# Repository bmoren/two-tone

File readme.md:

# two tone

I wanted to work on building a simple module from start to finish to test out some panel fab ideas and I thought a LPG/LPF would be a good candidate. After listening to Why We Bleep Ep.2 with Abstract Data and talking about the character of imperfection in analog circuits, I thought making a DIY vactrol based board would be interesting! I also thought if there were 2 halves, you could use slightly different components and vary each to make them truly distinct from one another. You can get different characteristics in the filter depending on the size and material of the LPF capacitor and the LDR/LED combo or vactrol used.

Shout out to [Look Mum No Computer](https://www.youtube.com/watch?v=Ch9w5JtbZSc) and [Meng Qi](https://www.mengqimusic.com/) for the initial inspiration for this module!
Thanks to [Josh Mason](http://www.joshmason.info/) for the Front Panel Express panel versions.

[Panel font by Alice Savoie / CNAP 19 CC BY-ND 4.0](http://cnap.graphismeenfrance.fr/faune/en.html)

more discussion of this project [on llllllll.co](https://llllllll.co/t/prototyping-two-tone-a-2x-passive-lowpass-gate-and-filter-with-diy-vactrols/12663)

### BOM:

| Quantity    | Component     |
| :------------- | :------------- |
| 2| Song Huei tall trimmer pots, A10k is prefered (B10k works, but the taper is compressed) |
| 6 | thonkikonn mono jacks |
| 2 | 3mm LED's (White or Blue are best) |
| 2 | Capacitors, 0.1uf - 4.7uf works best. |
| 4 | 6.8k ohm resistors |
| 2 | DIY or NLS-32 vactrol |

### How to build a DIY vactrol:

http://guitarpcb.com/PDF%20Files/DIY%20Vactrol.pdf
<br>
https://www.youtube.com/watch?v=Je5FS1A7Ys0
<br>
https://www.youtube.com/watch?v=Ch9w5JtbZSc
<br>
https://www.youtube.com/watch?v=VZ1B0Epr770

The way I usually do it is to take some small heat shrink and heat shrink each leg of the LDR and LED and then hold the LDR and LED together with the light emitting and light sensing parts touching. Cover them in more heat shrink and heat! This way the large heat shrink holds them together while the small heat shrink on each leg prevents shorts.

for each DIY vactrol, I use:

| Quantity      |Component     |
| :------------- | :------------- |
|1|LDR – GL5549 – 45~140(kOhm) |
|1 | 5mm White LED|

---

[CC-BY-SA-4.0](https://creativecommons.org/licenses/by-sa/4.0/).    
Build and use at your own risk! I am not responsible for any damage to self or otherwise that arises from using this project!

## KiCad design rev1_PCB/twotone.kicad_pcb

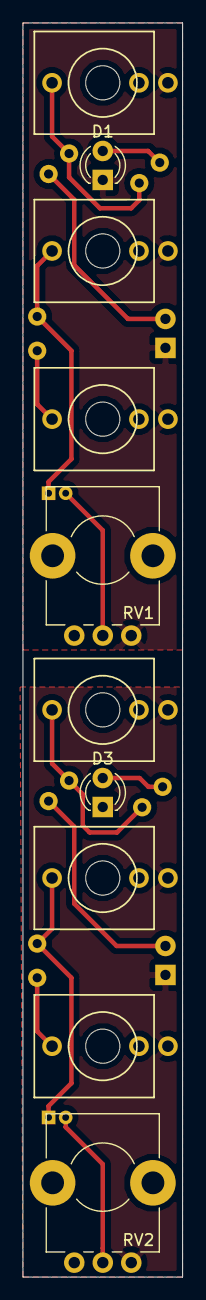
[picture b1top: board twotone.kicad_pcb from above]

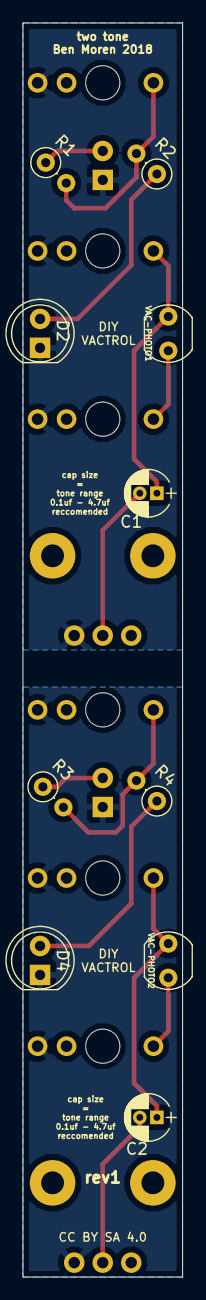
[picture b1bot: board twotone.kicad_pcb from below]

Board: 2 copper layers, 14.0 x 110.0 mm, 20 parts (10 on the bottom side), 14 nets.

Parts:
C1, C2: < 4.7u; CP_Radial_D4.0mm_P1.50mm
D1, D3: LED; LED_D3.0mm_center_anchor
D2, D4: VAC-LED; LED_D5.0mm
J1, J2, J3, J4, J5, J6: thonkiconn; PJ301M12_nearness
R1, R2, R3, R4: 6.8k; R_Axial_DIN0207_L6.3mm_D2.5mm_P2.54mm_Vertical
RV1, RV2: A10K; Potentiometer_Alps_RK09K_Horizontal_3d
VAC-PHOTO1, VAC-PHOTO2: 45k-140k1; Resistor_LDR_5x4.1_RM3

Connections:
GND: D3.1, D4.1, J4.1, J5.1, J6.1, RV2.1
GNDREF: D1.1, D2.1, J1.1, J2.1, J3.1, RV1.1
unnamed: C1.1, J2.3, VAC-PHOTO1.2
unnamed: C1.2, RV1.2
unnamed: C2.1, J5.3, VAC-PHOTO2.2
unnamed: C2.2, RV2.2
unnamed: D1.2, R1.1
unnamed: D2.2, R2.1
unnamed: D3.2, R3.1
unnamed: D4.2, R4.1
unnamed: J1.3, R1.2, R2.2
unnamed: J3.3, VAC-PHOTO1.1
unnamed: J4.3, R3.2, R4.2
unnamed: J6.3, VAC-PHOTO2.1

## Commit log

2018-06-07 init
2018-06-07 cleanup
2018-06-07 clean
2018-06-07 vactrol components
2018-06-07 fix table
2018-06-07 title size
2021-02-24 add Front Panel Express panels, courtesy of @jwm
2021-02-24 add attribution
